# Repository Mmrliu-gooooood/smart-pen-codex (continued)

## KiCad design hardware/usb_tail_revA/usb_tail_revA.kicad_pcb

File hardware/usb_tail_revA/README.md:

# USB 尾板 Rev A：已布通的候选，4项真实DRC仍未关闭 — NO FAB

2026-10-28 独立新板，不改主板B/C/D。12×20mm、0.8mm四层是工程候选，**不是170mm整笔装配通过**。

## 已完成与当前真实检查
- 原生根 `usb_tail_revA.kicad_sch`＋`usb_entry.kicad_sch`；PCB `usb_tail_revA.kicad_pcb`。9个真实器件/接口、37个符号pin、40个电气铜pad（含4同号S1壳脚），全部物理赋网并布线。
- 新ERC **0错误/0警告**；native PCB **0未连接、0原理图parity问题**。
- **4项DRC孔净距错误仍保留**：GCT推荐图/库原几何的两个定位NPTH孔，各邻两个同位不同编号GND pad，实际净距约0.1944mm，小于本项目0.25mm孔净距。不是新增线路短路；没有排除、不改全局规则把报告变绿。需板厂针对原厂landpattern确认工艺或做正式封装调整后重审。
- `tools/verify.py` 167个独立断言：所有真实PCB pad对XML、TI通道/直通pad网络、GCT官方位置/孔槽/焊盘尺寸、DQA官方铜尺寸、无DRC排除及上述真实剩余错误。`verification.json`/`verification_run.log`保存新结果。
- `review.pdf`及`preview/board.svg`/`back.svg`均由实际KiCad导出。无Gerber制造放行。

## 器件/引脚纠正与明确来源

### J101 USB4105-GF-A-120
[官方GCT B4图](https://gct.co/files/drawings/usb4105.pdf)的订货格式不含“16P”；旧逻辑源的`USB4105-GF-A16P`是描述拼接，不是本板采购号。本候选选真实 `USB4105-GF-A-120`：1.20±0.15mm壳脚，相对0.8±0.1mm候选板厚，底侧伸出约0.15–0.65mm，必须计入尾部机械。默认0.95mm脚不保证最坏板厚下露脚。

官方表列SHELL=GND；KiCad库4个壳槽同电气号S1，均真实接地。A1/B12、A12/B1及两组VBUS的重合焊盘编号对应原厂接触结构，不是重复短接错误。SBU1/2保持NC。已核推荐焊盘宽/距、两个0.65mm定位孔和4个0.6mm宽槽；定位孔净距DRC尚未放行。连接器本体约8.94×7.35mm、板上高度3.31mm；支承、拔插载荷及pin-in-paste锡量尚需装配资格，不能只靠裸PCB承担壳体载荷。

### U102 TPD4E05U06DQAR
[TI Rev O](https://www.ti.com/lit/ds/symlink/tpd4e05u06.pdf) pin表：1/2/4/5为四个ESD通道，3/8接GND，6/7/9/10为芯片内部NC且明确允许可选直通PCB走线。本板用真实铜线将10↔1(DP)、9↔2(DM)、7↔4(CC1)、6↔5(CC2)相连；**不是假定芯片内部直通**。符号对应pad为passive NC_ROUTE，逐pin核对，未将no_connect冲突压掉。

旧通用USON库不是本芯片原厂landpattern。本板新增 `TI_DQA0010A_USON10_OfficialLandpattern`：信号铜0.565×0.2mm，3/8地铜0.565×0.4mm，左右中心跨度0.835mm，节距0.5mm，R0.05；来自RevO p29示例。0.025mm阻焊扩张和courtyard为显式工艺候选。**同文档还列DQA0010B，实际订购批次/package版本须核实，不能凭相同body宣称任意兼容**。

### D101 TPD1E10B06DYAR
使用 `TI_DYA0002A_SOD523_OfficialLandpattern`，不是原通用D_SOD523。铜几何继承已核TI DYA图候选；[官方datasheet](https://www.ti.com/lit/ds/symlink/tpd1e10b06.pdf)来源/hash见`source_records.json`。1接VBUS、2接GND。TVS/ESD并不构成持续过压、反接或USB-PD保护许可。

## 布线与真实外部接口
- R110/R111各5.1k±1%独立下拉；无Rp广告测量、无PD控制器。保持原USB100默认策略，不能凭两只Rd就消费1.5A/3A；整机枚举、授权500mA、挂起和VBUS浪涌电容仍由整机验证。
- R112/R113 **留主板，不在尾板重复**。USB_DP/DM是到主板串联电阻之前的网，不能接错为USB_DP_MCU/DM_MCU。
- TP101=DP、TP102=DM、TP103=VBUS_5V、TP104=GND，是真正1.5×2mm无钢网焊线land；不是为DRC虚造的测试点。四个外部电气端必须用合格线束/连接方案完成。丝印5V/DP/DM/G给装配识别。
- 连线线径、长度、绞合/屏蔽、阻抗、拉力释放和壳体固定未确定；本PCB的0未连接只验证板内，**不包含跨板线束**。
- DP/DM主要在F层；连接器重复针的短DM交叉在In2层，均参考连续In1地。B层地铺铜带少量CC低速走线避让；壳脚/TVS/ESD有真实地过孔。未宣称完整高速差分通道资格。
- 当前0.15mm信号线、0.15mm候选铜净距，信号过孔0.45/0.20mm、地/电源0.6/0.3mm；这些是明示工艺候选，不是板厂已接单承诺。DP/DM存在Type-C重复针支路、换层和焊线fanout；**stackup未确定，因此不能保证90Ω或时序/眼图**。原生USB为Full-Speed用途，仍需整段SI、插拔和ESD测试。

同名J101/U102/D101/R110/R111与主板统一图是同一物理USB功能分区，不应在整机BOM里买两套。尾板纠正的MPN/封装/NC直通属于明确变体；后续整机分板原理图需同步权威版本，不能不经核对直接合并重复引用号。

## 复现与放行门槛

```
./rebuild.sh       # 重建源、导出XML、重建PCB，再完整检查
./run_checks.sh    # 不重建，只对当前真实文件重新检查/导出
```

首次重建时先用`kicad-cli sch export netlist --format kicadxml ...`生成XML，再build_pcb。`run_checks.sh`固定使用可写/tmp XDG目录，不写只读home配置。没有原厂PDF或私有相机图片打包。

最小未决：4项真实孔净距DFM、DQA实购封装版本/装配钢网、USB及跨板线束stackup/SI、尾部壳体支承与尺寸、整机USB电流/挂起/浪涌验证。尚无采购、报价或整笔成本通过结论。

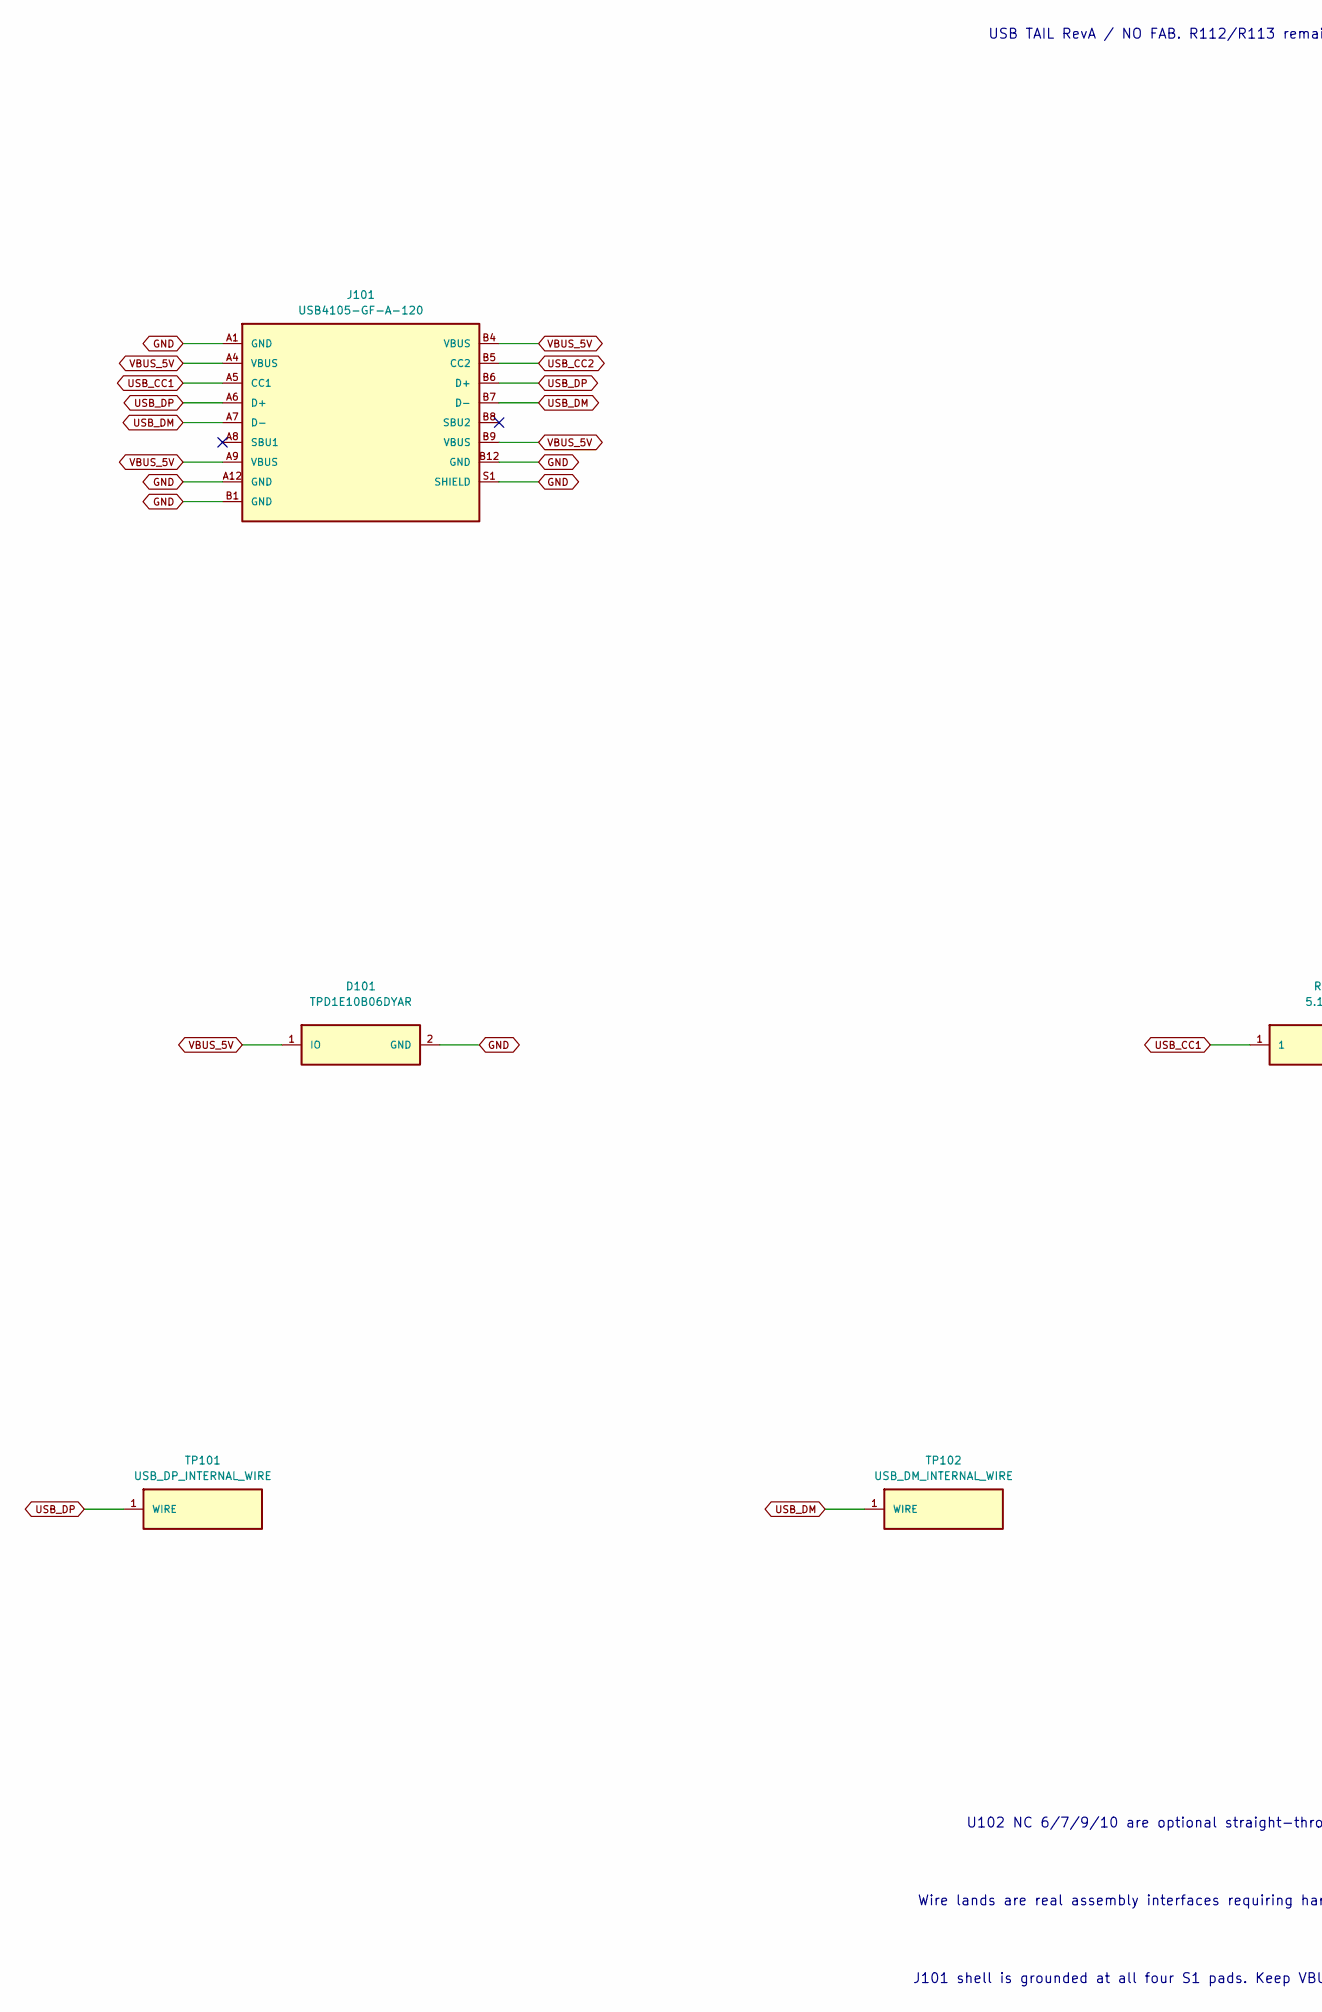
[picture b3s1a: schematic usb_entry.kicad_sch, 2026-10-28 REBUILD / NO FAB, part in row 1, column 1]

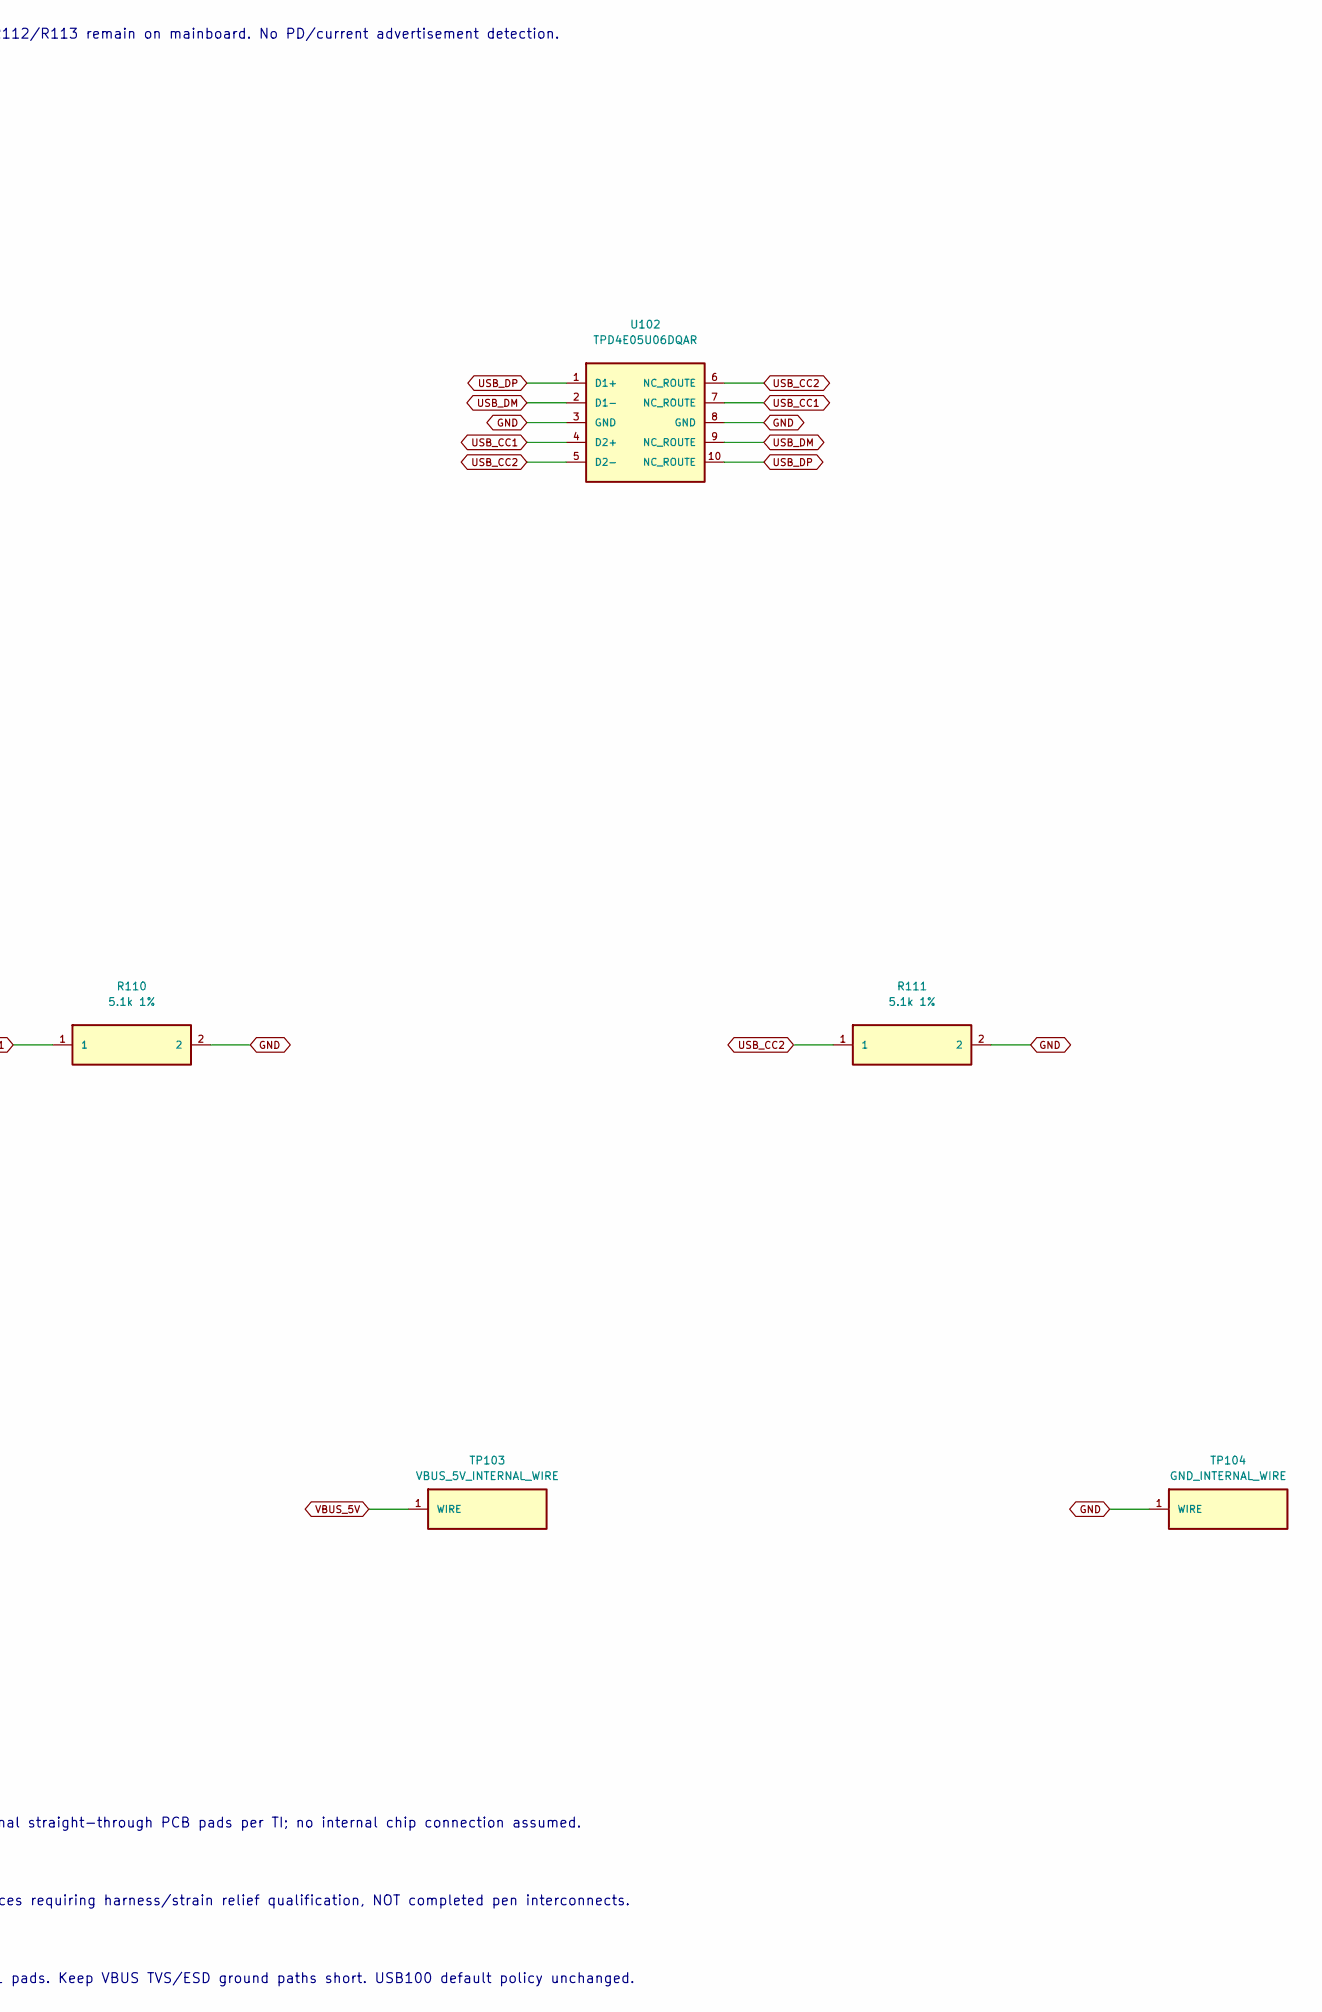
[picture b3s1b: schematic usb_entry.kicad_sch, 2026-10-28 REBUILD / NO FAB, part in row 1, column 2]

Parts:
D101: TPD1E10B06DYAR; TI_DYA0002A_SOD523_OfficialLandpattern
J101: USB4105-GF-A-120; USB_C_Receptacle_GCT_USB4105-xx-A_16P_TopMnt_Horizontal
R110, R111: 5.1k 1%; R_0603_1608Metric
TP101: USB_DP_INTERNAL_WIRE; WireLand_1.5x2_NoPaste
TP102: USB_DM_INTERNAL_WIRE; WireLand_1.5x2_NoPaste
TP103: VBUS_5V_INTERNAL_WIRE; WireLand_1.5x2_NoPaste
TP104: GND_INTERNAL_WIRE; WireLand_1.5x2_NoPaste
U102: TPD4E05U06DQAR; TI_DQA0010A_USON10_OfficialLandpattern

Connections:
GND: D101.2 (GND), J101.A1 (GND), J101.A12 (GND), J101.B1 (GND), J101.B12 (GND), J101.S1 (SHIELD), R110.2, R111.2, TP104.1, U102.3 (GND), U102.8 (GND)
USB_CC1: J101.A5 (CC1), R110.1, U102.4 (D2+), U102.7 (NC_ROUTE)
USB_CC2: J101.B5 (CC2), R111.1, U102.5 (D2-), U102.6 (NC_ROUTE)
USB_DM: J101.A7 (D-), J101.B7 (D-), TP102.1, U102.2 (D1-), U102.9 (NC_ROUTE)
USB_DP: J101.A6 (D+), J101.B6 (D+), TP101.1, U102.1 (D1+), U102.10 (NC_ROUTE)
VBUS_5V: D101.1 (IO), J101.A4 (VBUS), J101.A9 (VBUS), J101.B4 (VBUS), J101.B9 (VBUS), TP103.1

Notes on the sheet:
USB TAIL RevA / NO FAB. R112/R113 remain on mainboard. No PD/current advertisement detection.
U102 NC 6/7/9/10 are optional straight-through PCB pads per TI; no internal chip connection assumed.
Wire lands are real assembly interfaces requiring harness/strain relief qualification, NOT completed pen interconnects.
J101 shell is grounded at all four S1 pads. Keep VBUS TVS/ESD ground paths short. USB100 default policy unchanged.

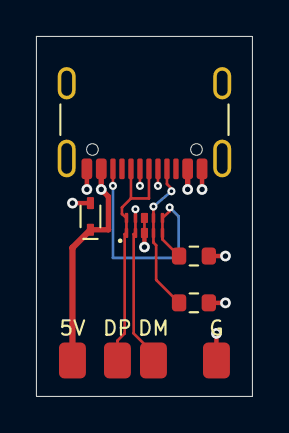
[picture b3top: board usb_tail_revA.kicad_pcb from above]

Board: 4 copper layers, 12.0 x 20.0 mm, 9 parts (0 on the bottom side), 6 nets.

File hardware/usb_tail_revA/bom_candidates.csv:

ref,value,footprint,assembly_status
D101,TPD1E10B06DYAR,SmartPen:TI_DYA0002A_SOD523_OfficialLandpattern,candidate no procurement
J101,USB4105-GF-A-120,Connector_USB:USB_C_Receptacle_GCT_USB4105-xx-A_16P_TopMnt_Horizontal,candidate no procurement
R110,5.1k 1%,Resistor_SMD:R_0603_1608Metric,candidate no procurement
R111,5.1k 1%,Resistor_SMD:R_0603_1608Metric,candidate no procurement
TP101,USB_DP_INTERNAL_WIRE,SmartPen:WireLand_1.5x2_NoPaste,wire interface requires harness/strain relief
TP102,USB_DM_INTERNAL_WIRE,SmartPen:WireLand_1.5x2_NoPaste,wire interface requires harness/strain relief
TP103,VBUS_5V_INTERNAL_WIRE,SmartPen:WireLand_1.5x2_NoPaste,wire interface requires harness/strain relief
TP104,GND_INTERNAL_WIRE,SmartPen:WireLand_1.5x2_NoPaste,wire interface requires harness/strain relief
U102,TPD4E05U06DQAR,SmartPen:TI_DQA0010A_USON10_OfficialLandpattern,candidate no procurement

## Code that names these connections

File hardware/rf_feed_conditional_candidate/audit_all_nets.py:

#!/usr/bin/env python3
import os,sys,pathlib,json,hashlib
os.environ['XDG_CONFIG_HOME']='/tmp/pen-rf-check/config'
import pcbnew as p
D=pathlib.Path(__file__).resolve().parent;S=D;sys.path.insert(0,str(D/'tools'));from physical_graph import graph
old=p.LoadBoard(str(S/'source_before.kicad_pcb'));b=p.LoadBoard(str(D/'mainboard_revD.kicad_pcb'));aa=graph(old);bb=graph(b)
def parts(g):return{r['net']:sorted(sorted(c)for c in r['components'])for r in g}
a,c=parts(aa),parts(bb)
changes=[net for net in a if a[net]!=c.get(net)]
if sorted(changes)!=['RF_ANT','RF_SIP']:raise RuntimeError('Unexpected actual pad partition change '+str(changes))
for net in ['RF_ANT','RF_SIP','GND','3V3_AON','SENS_VIO_1V8','STRAP_GPIO45','STRAP_GPIO46','CAM_SDA']:
 if len(c[net])!=1:raise RuntimeError('Disconnected '+net)
def geom(t):return[t.GetClass(),t.GetNetname(),t.GetLayer(),t.GetStart().x,t.GetStart().y,t.GetEnd().x,t.GetEnd().y,t.GetWidth(p.F_Cu)if isinstance(t,p.PCB_VIA)else t.GetWidth()]
a={t.m_Uuid.AsString():geom(t)for t in old.GetTracks()};c={t.m_Uuid.AsString():geom(t)for t in b.GetTracks()}
def padgeom(f):return[f.GetLayer(),f.GetPosition().x,f.GetPosition().y,f.GetOrientationDegrees(),f.GetFPIDAsString(),sorted((x.GetNumber(),x.GetNetname(),x.GetPosition().x,x.GetPosition().y,x.GetSize().x,x.GetSize().y)for x in f.Pads())]
fps={f.GetReference():padgeom(f)for f in b.GetFootprints()};moved=[f.GetReference()for f in old.GetFootprints()if padgeom(f)!=fps.get(f.GetReference())]
if sorted(moved)!=['C106','C107','L101','R104']:raise RuntimeError('Unexpected changed footprints '+str(moved))
result=dict(status='ACTUAL_PAD_CONNECTIVITY_CLOSED_EXCEPT_INHERITED_EN1_NOFAB',source_sha256=hashlib.sha256((S/'source_before.kicad_pcb').read_bytes()).hexdigest(),candidate_sha256=hashlib.sha256((D/'mainboard_revD.kicad_pcb').read_bytes()).hexdigest(),changed_partitions=changes,physical_graph=bb,moved_footprints=sorted(moved),removed=[dict(uuid=u,before=a[u])for u in sorted(a.keys()-c.keys())],modified=[dict(uuid=u,before=a[u],after=c[u])for u in sorted(a.keys()&c.keys())if a[u]!=c[u]],added=[dict(uuid=u,after=c[u])for u in sorted(c.keys()-a.keys())])
print(json.dumps(result,indent=2,sort_keys=True))

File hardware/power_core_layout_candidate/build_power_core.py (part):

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add('J4','PROTECTED PACK ONLY','Connector_Generic','Conn_01x02',205,125,{'1':'PACK_PLUS_PROTECTED','2':'GND'})
add('J5','SAFE CONTROL / JP OPEN','Connector_Generic','Conn_01x04',205,65,{'1':'USB_EN1','2':'USB_EN2','3':'CE_PERMISSION_EXTERNAL','4':'GND'})
for r,y,n in [('#FLG01',40,'VBUS_5V'),('#FLG02',55,'GND')]:add(r,'PWR_FLAG','power','PWR_FLAG',30,y,{'1':n})
a,b=pin('U1',13),pin('C1',1);y=snap(35);wire(a,(a[0],y),(b[0],y),b);label('VBUS_5V',(b[0],y))
for net,pn,c in [('SYS_RAW',10,'C3'),('PACK_PLUS_PROTECTED',2,'C2')]:
 a,b=pin('U1',pn),pin(c,1);wire(a,(b[0],a[1]),b);label(net,(b[0],a[1]))
for pn,r,n in [(14,'R3','CHG_TMR'),(12,'R2','CHG_ILIM'),(16,'R1','CHG_ISET')]:
 a,b=pin('U1',pn),pin(r,1);wire(a,(b[0],a[1]),b);label(n,(b[0],a[1]))
for pn,lp,n in [(9,1,'SW_L1'),(7,2,'SW_L2')]:
 a,b=pin('U2',pn),pin('L1',lp);wire(a,(a[0],b[1]),b);label(n,(a[0],b[1]))
a,b,c=pin('U2',10),pin('U2',1),pin('C4',1);x=snap(250);wire(a,(x,a[1]),(x,b[1]),b);wire((x,a[1]),(c[0],a[1]),c);label('SYS_RAW',(c[0],a[1]))
pts=[pin('U2',6),pin('C5',1),pin('C6',1),pin('R7',1)];y=snap(60)
for a in pts:wire(a,(a[0],y))
xs=sorted({a[0] for a in pts});wire(*[(x,y) for x in xs]);label('3V3_AON',(xs[0],y))
a,b,c=pin('R7',2),pin('R8',1),pin('U2',4);mid=(a[0],snap(122));wire(a,mid,b);wire(c,(snap(320),c[1]),(snap(320),mid[1]),mid);label('REG_FB',mid)
a,b=pin('R6',2),pin('JP1',1);wire(a,b);label('CHARGE_DISABLE',(a[0],snap(192)))
from collections import Counter
unique=set();new=[];counts=Counter()
for g in graphics:
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text('J1: 外接真实NTC两线接口，型号/温度窗口/连接器待定。',12,145)
text('GND = 保护后PACK_MINUS；禁止连接裸CELL_MINUS绕过保护。',12,151)
text('3  专用GPIO接口 / 调试充电跳线',12,162,1.6)
text('USB_EN1 -> MCU GPIO18；USB_EN2 -> GPIO21；禁止复用UART。',12,230)
text('复位默认LOW/LOW=USB100；休眠/枚举/来源授权仍需系统验证。',12,237)
text('JP1为物理开路跳线，未批准电池/NTC前禁止短接。',12,244)
text('R1=8.66k: 91.12-113.73mA；R2=3.24k: 最坏536.23mA。',12,251)
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
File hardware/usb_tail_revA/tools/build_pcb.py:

#!/usr/bin/python3
from pathlib import Path
import pcbnew as p,xml.etree.ElementTree as E,json
D=Path(__file__).resolve().parents[1];x=E.parse(D/'usb_tail_revA.xml');b=p.BOARD();b.SetCopperLayerCount(4);b.GetDesignSettings().SetBoardThickness(p.FromMM(.8));nets={};mapping={}
def pt(x,y):return p.VECTOR2I(p.FromMM(x),p.FromMM(y))
for n in x.findall('./nets/net'):
 name=n.attrib['name'];ni=p.NETINFO_ITEM(b,name);b.Add(ni);nets[name]=ni
 for q in n:mapping[q.attrib['ref'],q.attrib['pin']]=name
pos={'J101':(6,3.675,180),'U102':(6,10.5,90),'D101':(3,10,90),'R110':(8.75,14.8,0),'R111':(8.75,12.2,0),'TP101':(4.5,18,0),'TP102':(6.5,18,0),'TP103':(2,18,0),'TP104':(10,18,0)};fps={}
root=__import__('re').search(r'\(uuid ([0-9a-f-]+)\)',(D/'usb_tail_revA.kicad_sch').read_text())[1]
for c in x.findall('./components/comp'):
 ref=c.attrib['ref'];fpname=c.findtext('footprint');lib,name=fpname.split(':');path=D/'SmartPen.pretty' if lib=='SmartPen' else Path('/usr/share/kicad/footprints')/(lib+'.pretty');f=p.FootprintLoad(str(path),name);assert f
 f.SetReference(ref);f.SetValue(c.findtext('value'));f.SetPosition(pt(*pos[ref][:2]));f.SetOrientationDegrees(pos[ref][2]);f.SetFPID(p.LIB_ID(lib,name));f.SetPath(p.KIID_PATH('/'+root+c.find('sheetpath').attrib['tstamps']+c.findtext('tstamps')));b.Add(f);fps[ref]=f
 f.Reference().SetVisible(False);f.Value().SetVisible(False)
 for a in f.Pads():
  if a.GetNumber():a.SetNet(nets[mapping[ref,a.GetNumber()]])
for a,z in [((0,0),(12,0)),((12,0),(12,20)),((12,20),(0,20)),((0,20),(0,0))]:
 s=p.PCB_SHAPE();s.SetShape(p.SHAPE_T_SEGMENT);s.SetStart(pt(*a));s.SetEnd(pt(*z));s.SetWidth(p.FromMM(.05));s.SetLayer(p.Edge_Cuts);b.Add(s)
def loc(r,pin):a=next(a for a in fps[r].Pads() if a.GetNumber()==str(pin));v=a.GetPosition();return(p.ToMM(v.x),p.ToMM(v.y))
def trace(n,points,layer=p.F_Cu,w=.15):
 for a,z in zip(points,points[1:]):
  t=p.PCB_TRACK(b);t.SetStart(pt(*a));t.SetEnd(pt(*z));t.SetWidth(p.FromMM(w));t.SetLayer(layer);t.SetNet(nets[n]);b.Add(t)
def via(n,x,y,d=.45,h=.2):
 v=p.PCB_VIA(b);v.SetPosition(pt(x,y));v.SetWidth(p.F_Cu,p.FromMM(d));v.SetDrill(p.FromMM(h));v.SetViaType(p.VIATYPE_THROUGH);v.SetLayerPair(p.F_Cu,p.B_Cu);v.SetNet(nets[n]);b.Add(v)
# Type-C USB2 duplicate D+/D- tails joined before the ESD device.
trace('USB_DP',[loc('J101','B6'),(5.25,9),(6.25,9),loc('J101','A6')])
trace('USB_DP',[(5.25,9),(4.75,9.5),(4.75,9.865),loc('U102',10)])
for pin,xx in [('A7',5.75),('B7',6.75)]:trace('USB_DM',[loc('J101',pin),(xx,8.3)]);via('USB_DM',xx,8.3)
trace('USB_DM',[(5.75,8.3),(6.75,8.3)],p.In2_Cu);trace('USB_DM',[(5.75,8.3),(5.5,8.55),(5.5,9.6)],p.In2_Cu);via('USB_DM',5.5,9.6);trace('USB_DM',[(5.5,9.6),loc('U102',9)])
# CC passive Rd; no advertisement measurement or PD controller.
trace('USB_CC1',[loc('J101','A5'),(7.25,8.2),(7.5,8.45),(7.5,8.6)]);via('USB_CC1',7.5,8.6);trace('USB_CC1',[(7.5,8.6),(6.5,9.45)],p.B_Cu);via('USB_CC1',6.5,9.45);trace('USB_CC1',[(6.5,9.45),loc('U102',7)])
trace('USB_CC2',[loc('J101','B5'),(4.25,8.3)]);via('USB_CC2',4.25,8.3);trace('USB_CC2',[(4.25,8.3),(4.25,12.3),(7.9,12.3),(7.9,10),(7.4,9.5)],p.B_Cu);via('USB_CC2',7.4,9.5);trace('USB_CC2',[(7.4,9.5),(7.4,9.715),loc('U102',6)])
# Actual copper directly joins optional NC routing pads to respective diode pads.
for net,a,z in [('USB_DP',10,1),('USB_DM',9,2),('USB_CC1',7,4),('USB_CC2',6,5),('GND',8,3)]:trace(net,[loc('U102',a),loc('U102',z)])
trace('USB_DP',[loc('U102',1),(4.9,10.985),(4.9,16.5),(4.5,16.9),loc('TP101',1)])
trace('USB_DM',[loc('U102',2),(5.4,10.985),(5.4,16.5),(6.5,17.6),loc('TP102',1)])
trace('USB_CC1',[loc('U102',4),(6.5,11.45),(6.65,11.6),(6.65,13.525),loc('R110',1)])
trace('USB_CC2',[loc('U102',5),(7,11.275),loc('R111',1)])
# Ground returns to continuous In1 and B zones; solder wire ground is a real external interface.
for r,pin,xx,yy in [('U102',3,6,11.7),('D101',2,2,9.26),('R110',2,10.5,14.8),('R111',2,10.5,12.2),('TP104',1,10,16.5),('J101','A1',9.2,8.5),('J101','A12',2.8,8.5)]:trace('GND',[loc(r,pin),(xx,yy)],w=.25);via('GND',xx,yy,.6,.3)
# Both USB VBUS groups feed a real TVS and output land, not a hidden supply flag.
for pin,xx in [('A4',8.4),('A9',3.6)]:trace('VBUS_5V',[loc('J101',pin),(xx,8.5)],w=.3);via('VBUS_5V',xx,8.5,.6,.3)
trace('VBUS_5V',[(3.6,8.5),(3.6,7),(4,6.6),(4,5),(8,5),(8,6.6),(8.4,7),(8.4,8.5)],p.In2_Cu,.3)
trace('VBUS_5V',[(3.6,8.5),(4,8.9),(4,10.74),loc('D101',1)],w=.3)
trace('VBUS_5V',[loc('D101',1),(2,11.74),loc('TP103',1)],w=.35)
for label,xx in [('5V',2),('DP',4.5),('DM',6.5),('G',10)]:
 t=p.PCB_TEXT(b);t.SetText(label);t.SetPosition(pt(xx,16.2));t.SetTextSize(pt(.8,.8));t.SetTextThickness(p.FromMM(.12));t.SetLayer(p.F_SilkS);b.Add(t)
for layer in [p.In1_Cu,p.B_Cu]:
 z=p.ZONE(b);z.SetLayer(layer);z.SetNet(nets['GND']);z.SetLocalClearance(p.FromMM(.15));z.SetMinThickness(p.FromMM(.15));z.SetPadConnection(p.ZONE_CONNECTION_FULL);o=z.Outline();o.NewOutline()
 for a,y in [(.3,.3),(11.7,.3),(11.7,19.7),(.3,19.7)]:o.Append(p.FromMM(a),p.FromMM(y))
 b.Add(z)
file=D/'usb_tail_revA.kicad_pcb';p.SaveBoard(str(file),b);b=p.LoadBoard(str(file));p.ZONE_FILLER(b).Fill(b.Zones());p.SaveBoard(str(file),b)
pro=D/'usb_tail_revA.kicad_pro';j=json.loads(pro.read_text());j['net_settings']['classes'][0]['clearance']=.15;j['board']['design_settings']['rules']['min_via_diameter']=.45;j['board']['design_settings']['rules']['min_through_hole_diameter']=.2;j['board']['design_settings']['rules']['min_via_annular_width']=.125;j['board']['design_settings']['drc_exclusions']=[];pro.write_text(json.dumps(j,indent=2));print('Native PCB9footprints. Run DRC/real-pad check; no impedance release.')
